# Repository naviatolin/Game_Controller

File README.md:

# Game_Controller
With the rising popularity of lifestyle video games and lack of game consoles on the market during this pandemic, I created a USB powered game controller that could interface with the popular game: Stardew Valley.

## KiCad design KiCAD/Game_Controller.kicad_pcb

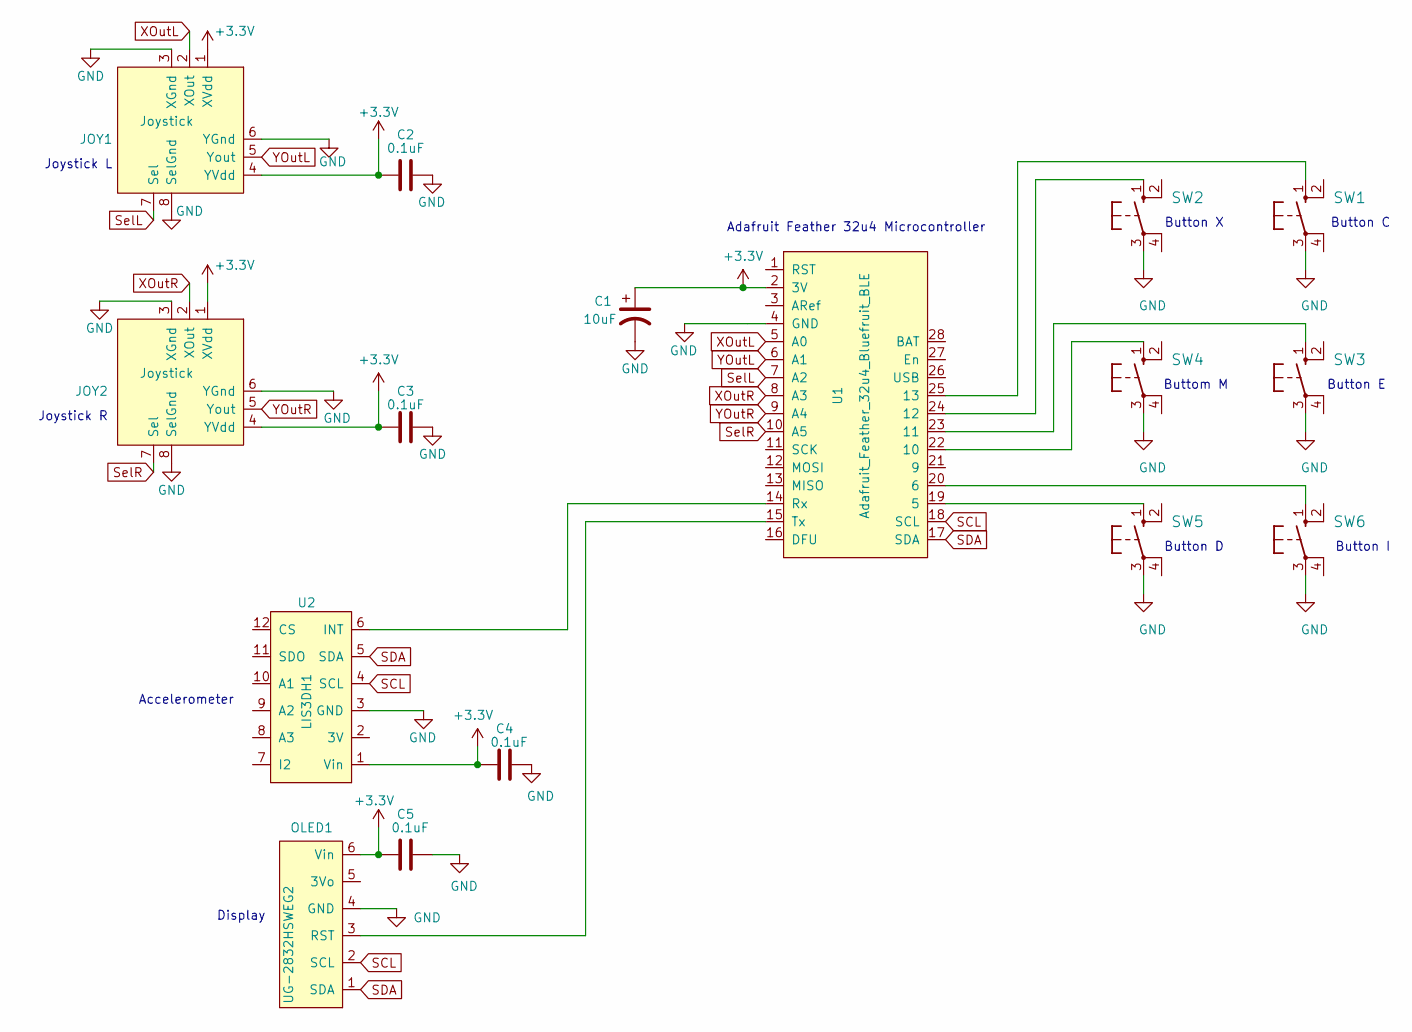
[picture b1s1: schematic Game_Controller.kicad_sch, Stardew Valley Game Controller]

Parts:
C1: 10uF; CP_Radial_D5.0mm_P2.50mm
C2, C3, C4, C5: 0.1uF; C_Rect_L4.0mm_W2.5mm_P2.50mm
JOY1, JOY2: Joystick; JOYSTICK
OLED1: UG-2832HSWEG2; OLED
SW1, SW2, SW3, SW4, SW5, SW6: B3F-1; B3F-40XX
U1: Adafruit_Feather_32u4_Bluefruit_BLE; FEATHERWING_DIM
U2: LIS3DH1; Accelerometer

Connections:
+3V3: C1.1, C2.2, C3.1, C4.1, C5.1, JOY1.1 (XVdd), JOY1.4 (YVdd), JOY2.1 (XVdd), JOY2.4 (YVdd), OLED1.6 (Vin), U1.2 (3V), U2.1 (Vin)
GND: C1.2, C2.1, C3.2, C4.2, C5.2, JOY1.3 (XGnd), JOY1.6 (YGnd), JOY1.8 (SelGnd), JOY2.3 (XGnd), JOY2.6 (YGnd), JOY2.8 (SelGnd), OLED1.4 (GND), SW1.3, SW2.3, SW3.3, SW4.3, SW5.3, SW6.3, U1.4 (GND), U2.3 (GND)
unnamed: OLED1.3 (RST), U1.15 (Tx)
unnamed: SW1.1 (S), U1.25 (13)
unnamed: SW2.1 (S), U1.24 (12)
unnamed: SW3.1 (S), U1.23 (11)
unnamed: SW4.1 (S), U1.22 (10)
unnamed: SW5.1 (S), U1.19 (5)
unnamed: SW6.1 (S), U1.20 (6)
unnamed: U1.14 (Rx), U2.6 (INT)
SCL: OLED1.2 (SCL), U1.18 (SCL), U2.4 (SCL)
SDA: OLED1.1 (SDA), U1.17 (SDA), U2.5 (SDA)
SelL: JOY1.7 (Sel), U1.7 (A2)
SelR: JOY2.7 (Sel), U1.10 (A5)
XOutL: JOY1.2 (XOut), U1.5 (A0)
XOutR: JOY2.2 (XOut), U1.8 (A3)
YOutL: JOY1.5 (Yout), U1.6 (A1)
YOutR: JOY2.5 (Yout), U1.9 (A4)

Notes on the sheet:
Joystick R
Joystick L
Accelerometer
Display
Adafruit Feather 32u4 Microcontroller
Button X
Button D
Buttom M
Button E
Button C
Button I

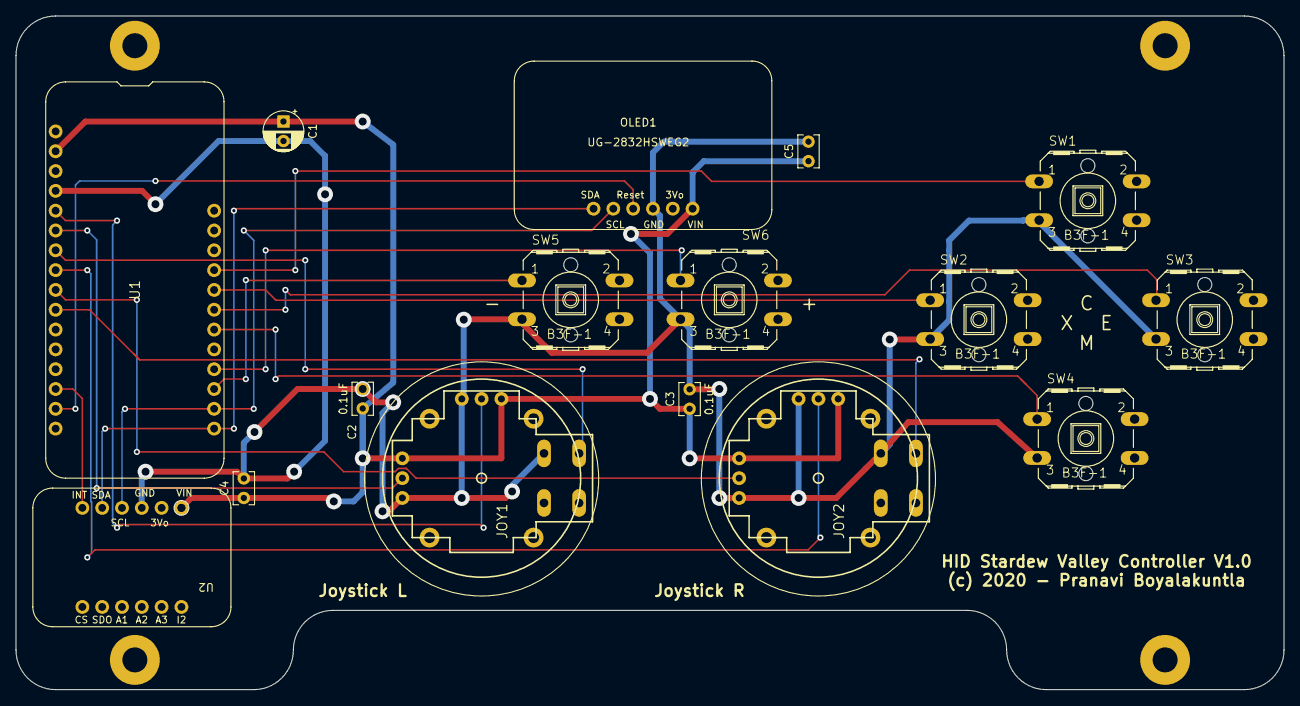
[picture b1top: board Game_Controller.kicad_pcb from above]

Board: 2 copper layers, 162.6 x 86.4 mm, 16 parts (0 on the bottom side), 18 nets.

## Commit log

2020-12-19 All firmware and KiCAD files

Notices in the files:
KiCAD/Game_Controller.kicad_pcb:
(c) 2020 - Pranavi Boyalakuntla
